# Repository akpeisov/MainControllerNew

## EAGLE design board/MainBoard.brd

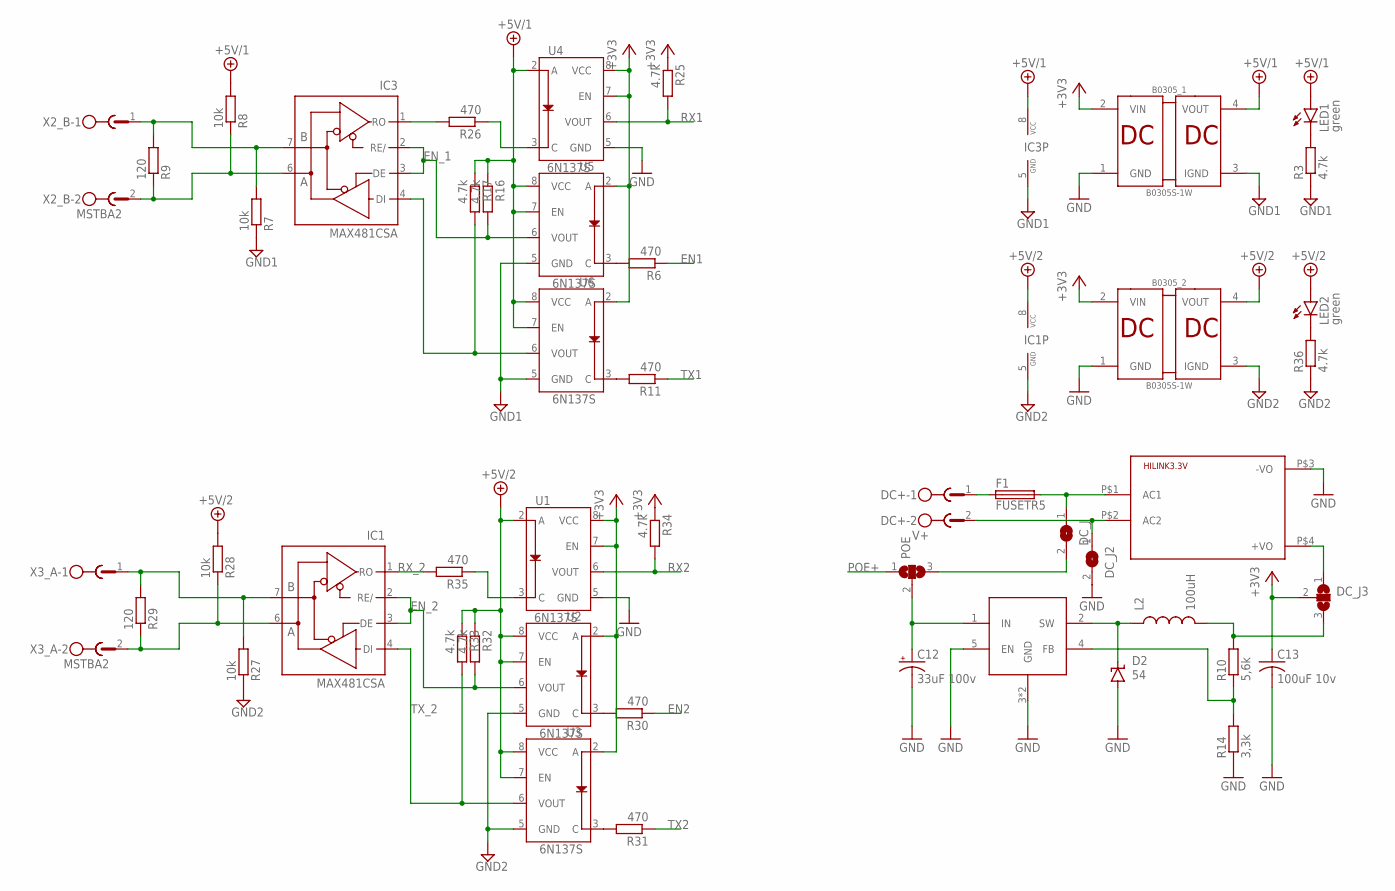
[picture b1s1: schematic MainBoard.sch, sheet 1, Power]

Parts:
B0305_1, B0305_2: B0305S-1W; B_S-1W
C12: 33uF 100v; 150CLZ-0810
C13: 100uF 10v; C1206
D2: 54; SMBJ
DC+: V+; MSTBA2
DC_J, DC_J2: SJW
DC_J3: SJ2W; SJ_2
F1: FUSETR5; TR5
HILINK3.3V: HLK-PM013W; HLK-PM01
IC1, IC3: MAX481CSA; SO08
L2: 100uH; CR75
LED1, LED2: green; SML1206
POE: SJ2W; SJ_2
R3, R16, R17, R25, R32, R33, R34, R36: 4.7k; R0805
R6, R11, R26, R30, R31, R35: 470; R0805
R7, R8, R27, R28: 10k; R0805
R9, R29: 120; R0805
R10: 5,6k; R0805
R14: 3,3k; R0805
U1, U2, U3, U4, U5, U6: 6N137S; 8-SMD
U9: XL7015; TO252-51
X2_B, X3_A: MSTBA2

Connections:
+3V3: B0305_1.2 (VIN), B0305_2.2 (VIN), C13.1, DC_J3.2, R25.1, R34.1, U1.7 (EN), U1.8 (VCC), U2.2 (A), U3.2 (A), U4.7 (EN), U4.8 (VCC), U5.2 (A), U6.2 (A); also elsewhere on the board
+5V/1: B0305_1.4 (VOUT), IC3.8 (VCC), LED1.A, R8.2, R16.1, R17.1, U4.2 (A), U5.7 (EN), U5.8 (VCC), U6.7 (EN), U6.8 (VCC)
+5V/2: B0305_2.4 (VOUT), IC1.8 (VCC), LED2.A, R28.2, R32.1, R33.1, U1.2 (A), U2.7 (EN), U2.8 (VCC), U3.7 (EN), U3.8 (VCC)
EN1: R6.1; also elsewhere on the board
EN2: R30.1; also elsewhere on the board
EN_1: IC3.2 (RE/), IC3.3 (DE), R16.2, U5.6 (VOUT)
EN_2: IC1.2 (RE/), IC1.3 (DE), R32.2, U2.6 (VOUT)
GND: B0305_1.1 (GND), B0305_2.1 (GND), C12.-, C13.2, D2.A, DC_J2.2, HILINK3.3V.P$3 (-VO), R14.1, U1.5 (GND), U4.5 (GND), U9.3 (GND), U9.5 (EN), U9.GND; also elsewhere on the board
GND1: B0305_1.3 (IGND), IC3.5 (GND), R3.1, R7.1, U5.5 (GND), U6.5 (GND)
GND2: B0305_2.3 (IGND), IC1.5 (GND), R27.1, R36.1, U2.5 (GND), U3.5 (GND)
unnamed: LED1.C, R3.2
unnamed: IC3.7 (B), R7.2, R9.2, X2_B.1
unnamed: IC3.6 (A), R8.1, R9.1, X2_B.2
unnamed: R10.1, R14.2, U9.4 (FB)
unnamed: DC_J.2, POE.3
unnamed: D2.C, L2.P$1 (1), U9.2 (SW)
unnamed: DC+.2, DC_J2.1, HILINK3.3V.P$2 (AC2)
unnamed: DC+.1, F1.1
unnamed: DC_J3.3, L2.P$2 (2), R10.2
unnamed: R6.2, U5.3 (C)
unnamed: R11.2, U6.3 (C)
unnamed: IC1.7 (B), R27.2, R29.2, X3_A.1
unnamed: R26.1, U4.3 (C)
unnamed: IC1.6 (A), R28.1, R29.1, X3_A.2
unnamed: R30.2, U2.3 (C)
unnamed: R31.2, U3.3 (C)
unnamed: R35.1, U1.3 (C)
unnamed: LED2.C, R36.2
unnamed: DC_J3.1, HILINK3.3V.P$4 (+VO)
unnamed: C12.+, POE.2, U9.1 (IN)
unnamed: DC_J.1, F1.2, HILINK3.3V.P$1 (AC1)
POE+: POE.1; also elsewhere on the board
RX1: R25.2, U4.6 (VOUT); also elsewhere on the board
RX2: R34.2, U1.6 (VOUT); also elsewhere on the board
RX485: IC3.1 (RO), R26.2
RX_2: IC1.1 (RO), R35.2
TX1: R11.1; also elsewhere on the board
TX2: R31.1; also elsewhere on the board
TX485: IC3.4 (DI), R17.2, U6.6 (VOUT)
TX_2: IC1.4 (DI), R33.2, U3.6 (VOUT)

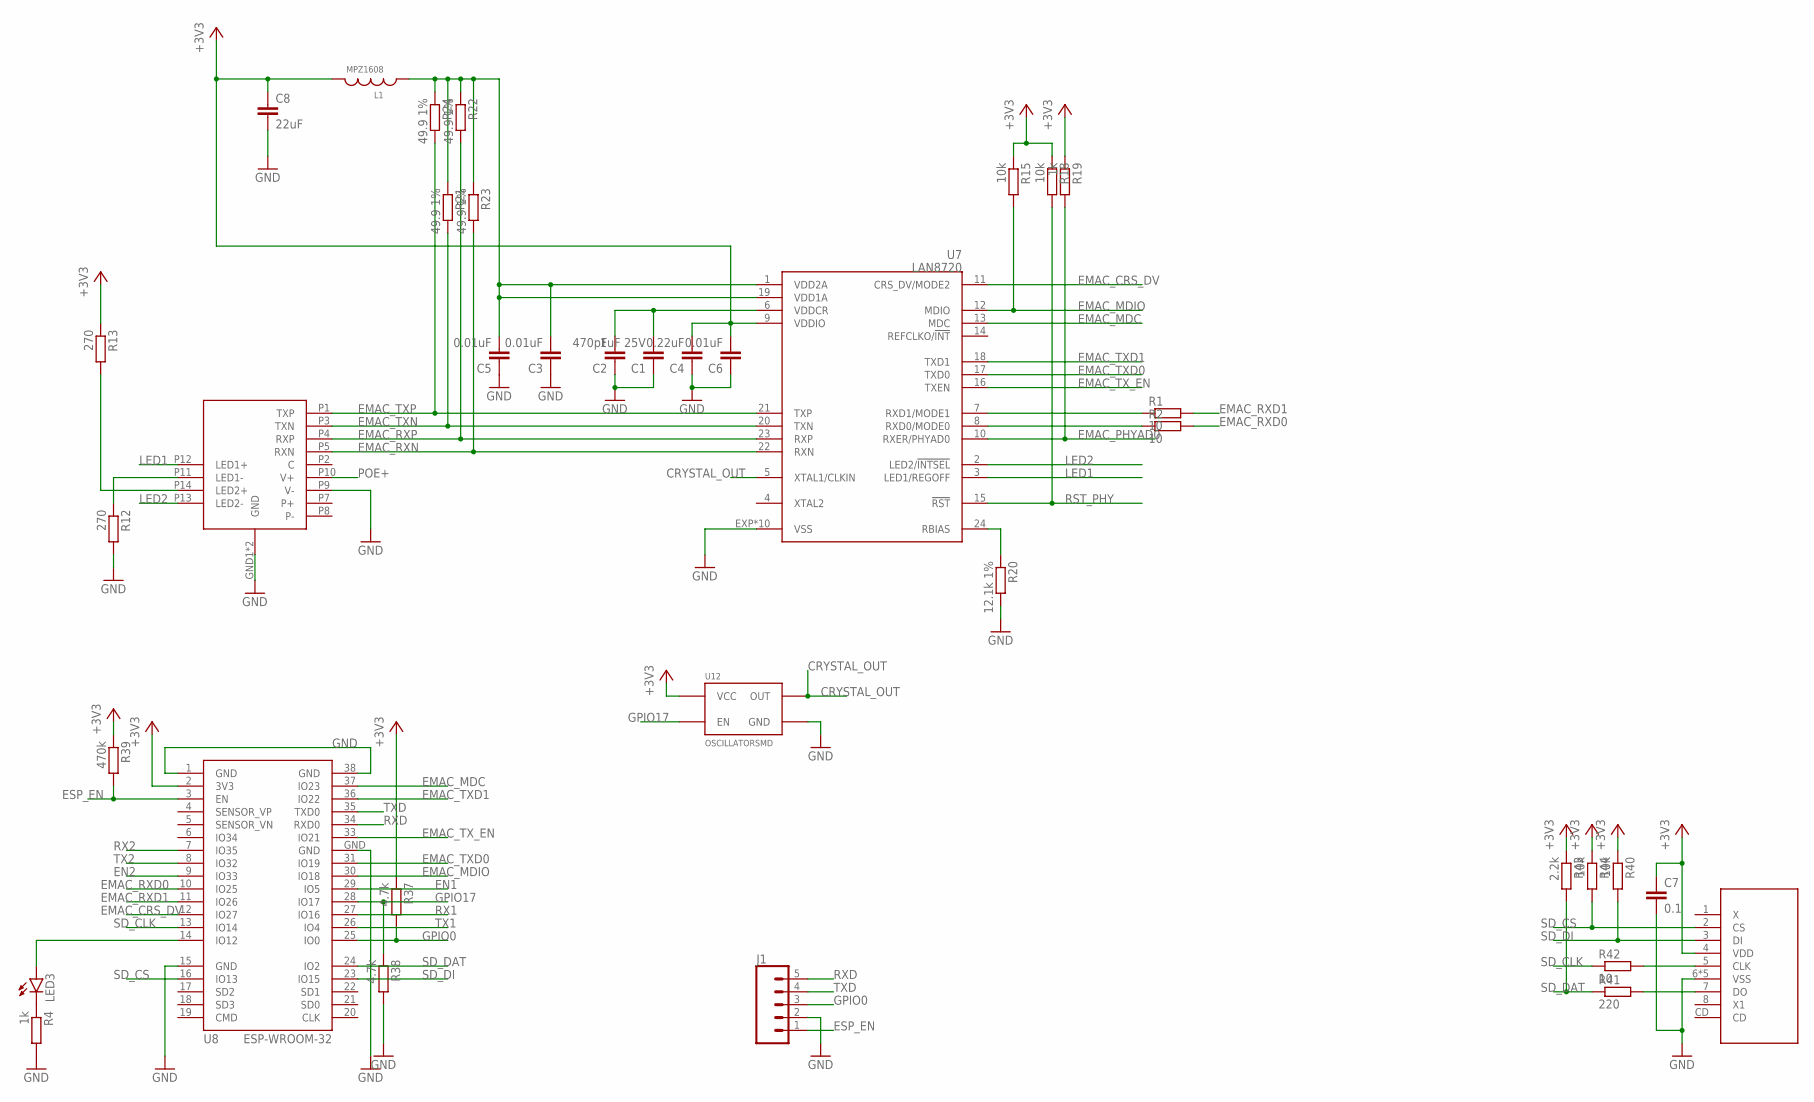
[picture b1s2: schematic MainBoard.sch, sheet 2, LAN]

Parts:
C1: 1uF 25V; C0805; MPN CC0603KPX7R8BB105
C2: 470pF; C0805; MPN CC0603JRX7R7BB471
C3, C5, C6: 0.01uF; C0805; MPN CC0603KRX7R6BB103
C4: 0.22uF; C0805; MPN CC0603KRX7R6BB103
C7: 0.1; C1206
C8: 22uF; C0805; MPN CC0603MPX5R5BB226
J1: CONN_05LOCK; 1X05_LOCK
L1: MPZ1608; 1608
LED3: LEDSML1206; SML1206
R1, R2, R42: 10; R0805; MPN RC0603JR-0727RL
R4: 1k; R0805; MPN RC0603JR-07240RL
R12, R13: 270; R0805; MPN RC0603JR-07240RL
R15, R18, R40, R44: 10k; R0805; MPN RC0603JR-0727RL
R19: 1k; R0805; MPN RC0603JR-0727RL
R20: 12.1k 1%; R0805; MPN RC0603JR-0727RL
R21, R22, R23, R24: 49.9 1%; R0805; MPN RC0603JR-0727RL
R37, R38: 4.7k; R0805; MPN RC0603JR-07240RL
R39: 470k; R0805; MPN RC0603JR-07240RL
R41: 220; R0805; MPN RC0603JR-0727RL
R43: 2.2k; R0805; MPN RC0603JR-0727RL
U7: LAN8720; QFN24; MPN LAN8720A-CP-ABC
U8: ESP-WROOM-32
U12: OSCILLATORSMD; CRYSTAL-SMD-7X5
U$1: MICROSD; MICROSDCARD
U$2: RJ45-1169

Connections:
+3V3: C4.2, C6.2, C7.1, C8.1, L1.P$2, R13.1, R15.1, R18.1, R19.1, R37.1, R39.1, R40.1, R43.1, R44.1, U7.9 (VDDIO), U8.2 (3V3), U12.P$4 (VCC), U$1.4 (VDD); also elsewhere on the board
CRYSTAL_OUT: U7.5 (XTAL1/CLKIN), U12.P$3 (OUT)
EMAC_CRS_DV: U7.11 (CRS_DV/MODE2), U8.12 (IO27)
EMAC_MDC: U7.13 (MDC), U8.37 (IO23)
EMAC_MDIO: R15.2, U7.12 (MDIO), U8.30 (IO18)
EMAC_PHYAD0: R19.2, U7.10 (RXER/PHYAD0)
EMAC_RBIAS: R20.1, U7.24 (RBIAS)
EMAC_RXD0: R2.2, U8.10 (IO25)
EMAC_RXD0_LAN: R2.1, U7.8 (RXD0/MODE0)
EMAC_RXD1: R1.2, U8.11 (IO26)
EMAC_RXD1_LAN: R1.1, U7.7 (RXD1/MODE1)
EMAC_RXN: R23.2, U7.22 (RXN), U$2.P5 (RXN)
EMAC_RXP: R22.2, U7.23 (RXP), U$2.P4 (RXP)
EMAC_TXD0: U7.17 (TXD0), U8.31 (IO19)
EMAC_TXD1: U7.18 (TXD1), U8.36 (IO22)
EMAC_TXN: R21.2, U7.20 (TXN), U$2.P3 (TXN)
EMAC_TXP: R24.2, U7.21 (TXP), U$2.P1 (TXP)
EMAC_TX_EN: U7.16 (TXEN), U8.33 (IO21)
EMAC_VDDCR: C1.2, C2.2, U7.6 (VDDCR)
EMAC_VDDXA: C3.2, C5.2, L1.P$1, R21.1, R22.1, R23.1, R24.1, U7.1 (VDD2A), U7.19 (VDD1A)
EN1: U8.29 (IO5); also elsewhere on the board
EN2: U8.9 (IO33); also elsewhere on the board
ESP_EN: J1.1, R39.2, U8.3 (EN)
GND: C1.1, C2.1, C3.1, C4.1, C5.1, C6.1, C7.2, C8.2, J1.2, R4.2, R12.2, R20.2, R38.2, U7.EXP (VSS), U7.GND1 (VSS), U7.GND2 (VSS), U7.GND3 (VSS), U7.GND4 (VSS), U7.GND5 (VSS), U7.GND6 (VSS), U7.GND7 (VSS), U7.GND8 (VSS), U7.GND9 (VSS), U8.1 (GND), U8.15 (GND), U8.38 (GND), U8.GND, U12.P$2 (GND), U$1.6 (VSS), U$1.GND (VSS), U$1.GND1 (VSS), U$1.GND2 (VSS), U$1.GND3 (VSS), U$2.GND1 (GND), U$2.GND2 (GND), U$2.P9 (V-); also elsewhere on the board
GPIO0: J1.3, R37.2, U8.25 (IO0)
GPIO17: R38.1, U8.28 (IO17), U12.P$1 (EN)
LED1: U7.3 (LED1/REGOFF), U$2.P12 (LED1+)
LED2: U7.2 (LED2/!INTSEL), U$2.P13 (LED2-)
unnamed: R13.2, U$2.P14 (LED2+)
unnamed: R12.1, U$2.P11 (LED1-)
unnamed: LED3.A, U8.14 (IO12)
unnamed: LED3.C, R4.1
unnamed: R41.2, U$1.7 (DO)
unnamed: R42.2, U$1.5 (CLK)
POE+: U$2.P10 (V+); also elsewhere on the board
RST_PHY: R18.2, U7.15 (!RST)
RX1: U8.27 (IO16); also elsewhere on the board
RX2: U8.7 (IO35); also elsewhere on the board
RXD: J1.5, U8.34 (RXD0)
SD_CLK: R42.1, U8.13 (IO14)
SD_CS: R44.2, U8.16 (IO13), U$1.2 (CS)
SD_DAT: R41.1, R43.2, U8.24 (IO2)
SD_DI: R40.2, U8.23 (IO15), U$1.3 (DI)
TX1: U8.26 (IO4); also elsewhere on the board
TX2: U8.8 (IO32); also elsewhere on the board
TXD: J1.4, U8.35 (TXD0)

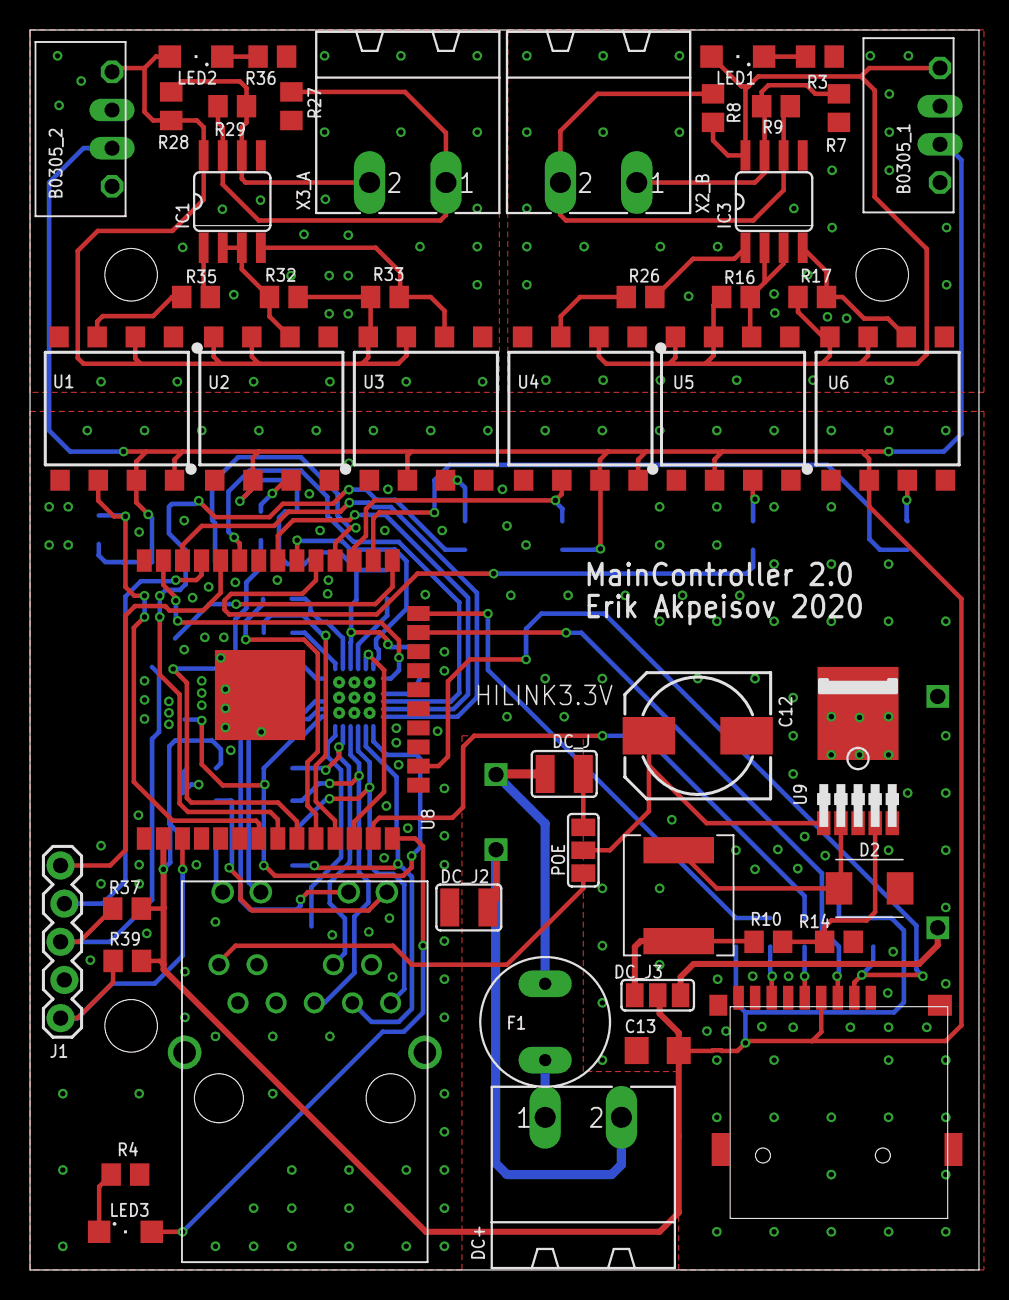
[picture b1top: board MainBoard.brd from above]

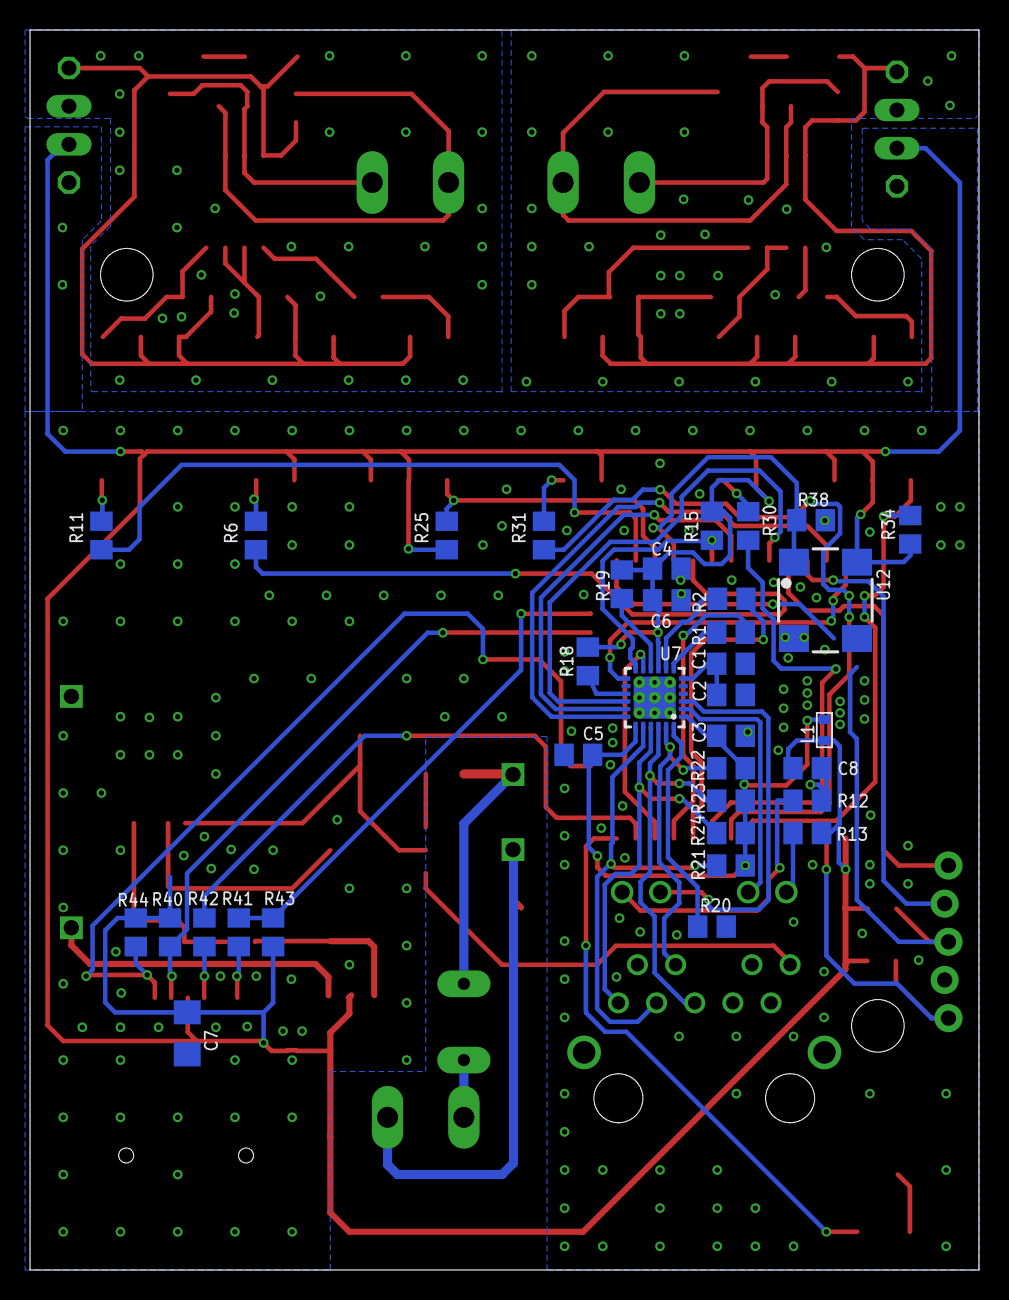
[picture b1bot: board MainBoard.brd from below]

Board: 2 copper layers, 63.2 x 82.5 mm, 85 parts (35 on the bottom side), 77 nets.

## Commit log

2020-09-16 OTA added
2020-09-16 some fixes
2020-09-21 added polling retries
2020-09-24 added switchOutput method
2020-10-02 added boards
2020-10-09 alice added
2020-10-15 ftp, dmx work
2020-12-19 ftp temp commit
2020-12-27 with mqtt and ftp
2020-12-27 +ftp +dmx +mqtt
2020-12-28 mqtt subscribe
2021-02-14 mqtt fix

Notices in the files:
parts and their libraries:
SparkFun-Passives: Licensing: Creative Commons ShareAlike 4.0 International - https://creativecommons.org/licenses/by-sa/4.0
esp32wroom: Creative Commons Attribution-ShareAlike 4.0 International
candel: (C) 2014 Tomasz Boleslaw CEDRO, cederom@tlen.pl, http://www.tomek.cedro.info.
